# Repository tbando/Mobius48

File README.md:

# Mobius48
* ErgoDox向けキーキャップセットを使った40%配列キーボードです

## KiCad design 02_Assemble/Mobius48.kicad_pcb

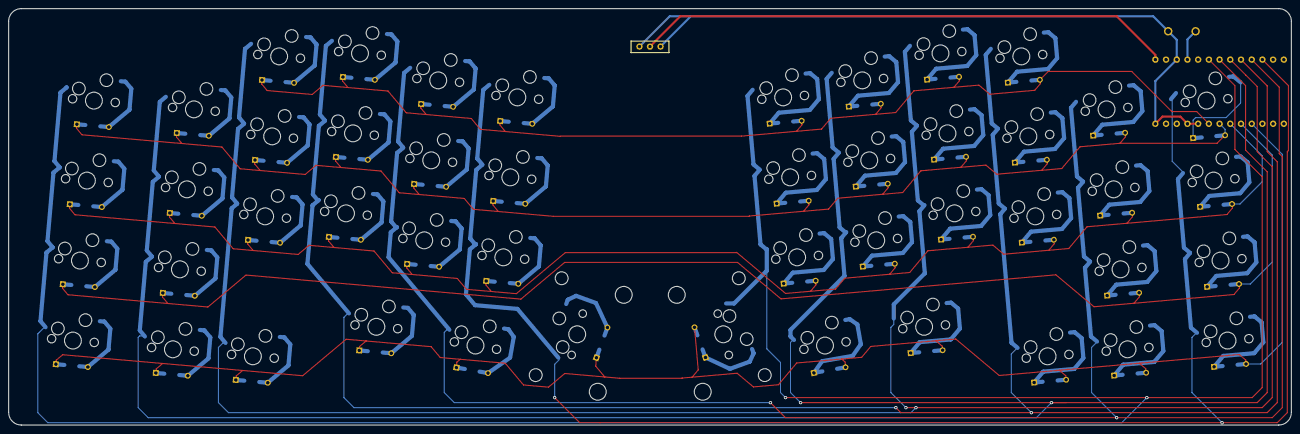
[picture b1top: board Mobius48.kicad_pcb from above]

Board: 2 copper layers, 304.4 x 98.8 mm, 99 parts (0 on the bottom side), 62 nets.

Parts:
D1, D2, D3, D4, D5, D6, D7, D8, D9, D10, D11, D12, D13, D14, D15, D16, D17, D18, D19, D20, D21, D22, D23, D24, D25, D26, D27, D28, D29, D30, D31, D32, D33, D34, D35, D36, D37, D38, D39, D40, D41, D42, D43, D44, D45, D46, D47, D48: D; Diode_TH_SMD
J1: Conn_01x02; Battery_XH2.5_GL_PCB
SW1, SW2, SW3, SW4, SW45, SW46, SW47, SW48: SW_PUSH; CherryMX_Hotswap_1.5u
SW5, SW6, SW7, SW8, SW9, SW10, SW11, SW12, SW13, SW14, SW15, SW16, SW17, SW18, SW19, SW20, SW21, SW22, SW23, SW25, SW26, SW27, SW29, SW30, SW31, SW32, SW33, SW34, SW35, SW36, SW37, SW38, SW39, SW40, SW41, SW42, SW43, SW44: SW_PUSH; CherryMX_Hotswap_1u
SW24, SW28: SW_PUSH; CherryMX_Hotswap_2u
SW49: SW_PUSH; ResetSW
U1: BLEMicroPro; Micon_BMP_GL

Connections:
Bat+: J1.1, U1.25 (BAT+)
Col0: SW1.1, SW2.1, SW3.1, SW4.1, SW25.1, SW26.1, SW27.1, SW28.1, U1.20 (F4/PIN20)
Col1: SW5.1, SW6.1, SW7.1, SW8.1, SW29.1, SW30.1, SW31.1, SW32.1, U1.19 (F5/PIN19)
Col2: SW9.1, SW10.1, SW11.1, SW12.1, SW33.1, SW34.1, SW35.1, SW36.1, U1.18 (F6/PIN18)
Col3: SW13.1, SW14.1, SW15.1, SW16.1, SW37.1, SW38.1, SW39.1, SW40.1, U1.17 (F7/PIN17)
Col4: SW17.1, SW18.1, SW19.1, SW20.1, SW41.1, SW42.1, SW43.1, SW44.1, U1.16 (B1/PIN16)
Col5: SW21.1, SW22.1, SW23.1, SW24.1, SW45.1, SW46.1, SW47.1, SW48.1, U1.15 (B3/PIN15)
GND: J1.2, SW49.2, U1.3 (GND), U1.4 (GND), U1.23 (GND), U1.26 (BAT-)
unnamed: D1.2 (A), SW1.2
unnamed: D2.2 (A), SW2.2
unnamed: D3.2 (A), SW3.2
unnamed: D4.2 (A), SW4.2
unnamed: D5.2 (A), SW5.2
unnamed: D6.2 (A), SW6.2
unnamed: D7.2 (A), SW7.2
unnamed: D8.2 (A), SW8.2
unnamed: D9.2 (A), SW9.2
unnamed: D10.2 (A), SW10.2
unnamed: D11.2 (A), SW11.2
unnamed: D12.2 (A), SW12.2
unnamed: D13.2 (A), SW13.2
unnamed: D14.2 (A), SW14.2
unnamed: D15.2 (A), SW15.2
unnamed: D16.2 (A), SW16.2
unnamed: D17.2 (A), SW17.2
unnamed: D18.2 (A), SW18.2
unnamed: D19.2 (A), SW19.2
unnamed: D20.2 (A), SW20.2
unnamed: D21.2 (A), SW21.2
unnamed: D22.2 (A), SW22.2
unnamed: D23.2 (A), SW23.2
unnamed: D24.2 (A), SW24.2
unnamed: D25.1 (K), SW25.2
unnamed: D26.1 (K), SW26.2
unnamed: D27.1 (K), SW27.2
unnamed: D28.1 (K), SW28.2
unnamed: D29.1 (K), SW29.2
unnamed: D30.1 (K), SW30.2
unnamed: D31.1 (K), SW31.2
unnamed: D32.1 (K), SW32.2
unnamed: D33.1 (K), SW33.2
unnamed: D34.1 (K), SW34.2
unnamed: D35.1 (K), SW35.2
unnamed: D36.1 (K), SW36.2
unnamed: D37.1 (K), SW37.2
unnamed: D38.1 (K), SW38.2
unnamed: D39.1 (K), SW39.2
unnamed: D40.1 (K), SW40.2
unnamed: D41.1 (K), SW41.2
unnamed: D42.1 (K), SW42.2
unnamed: D43.1 (K), SW43.2
unnamed: D44.1 (K), SW44.2
unnamed: D45.1 (K), SW45.2
unnamed: D46.1 (K), SW46.2
unnamed: D47.1 (K), SW47.2
unnamed: D48.1 (K), SW48.2
Reset: SW49.1, U1.22 (RST)
Row0: D9.1 (K), D13.1 (K), D17.1 (K), D21.1 (K), D25.2 (A), D29.2 (A), D33.2 (A), D37.2 (A), U1.5 (D1/PIN5/SDA)
Row1: D1.1 (K), D5.1 (K), D10.1 (K), D14.1 (K), D18.1 (K), D22.1 (K), D26.2 (A), D30.2 (A), D34.2 (A), D38.2 (A), D41.2 (A), D45.2 (A), U1.6 (D0/PIN6/SCL)
Row2: D2.1 (K), D6.1 (K), D11.1 (K), D15.1 (K), D19.1 (K), D23.1 (K), D27.2 (A), D31.2 (A), D35.2 (A), D39.2 (A), D42.2 (A), D46.2 (A), U1.7 (D4/PIN7)
Row3: D3.1 (K), D7.1 (K), D43.2 (A), D47.2 (A), U1.8 (C6/PIN8)
Row4: D4.1 (K), D8.1 (K), D12.1 (K), D16.1 (K), D20.1 (K), D24.1 (K), D28.2 (A), D32.2 (A), D36.2 (A), D40.2 (A), D44.2 (A), D48.2 (A), U1.9 (D7/PIN9)

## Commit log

2022-02-22 add qmk keymap
